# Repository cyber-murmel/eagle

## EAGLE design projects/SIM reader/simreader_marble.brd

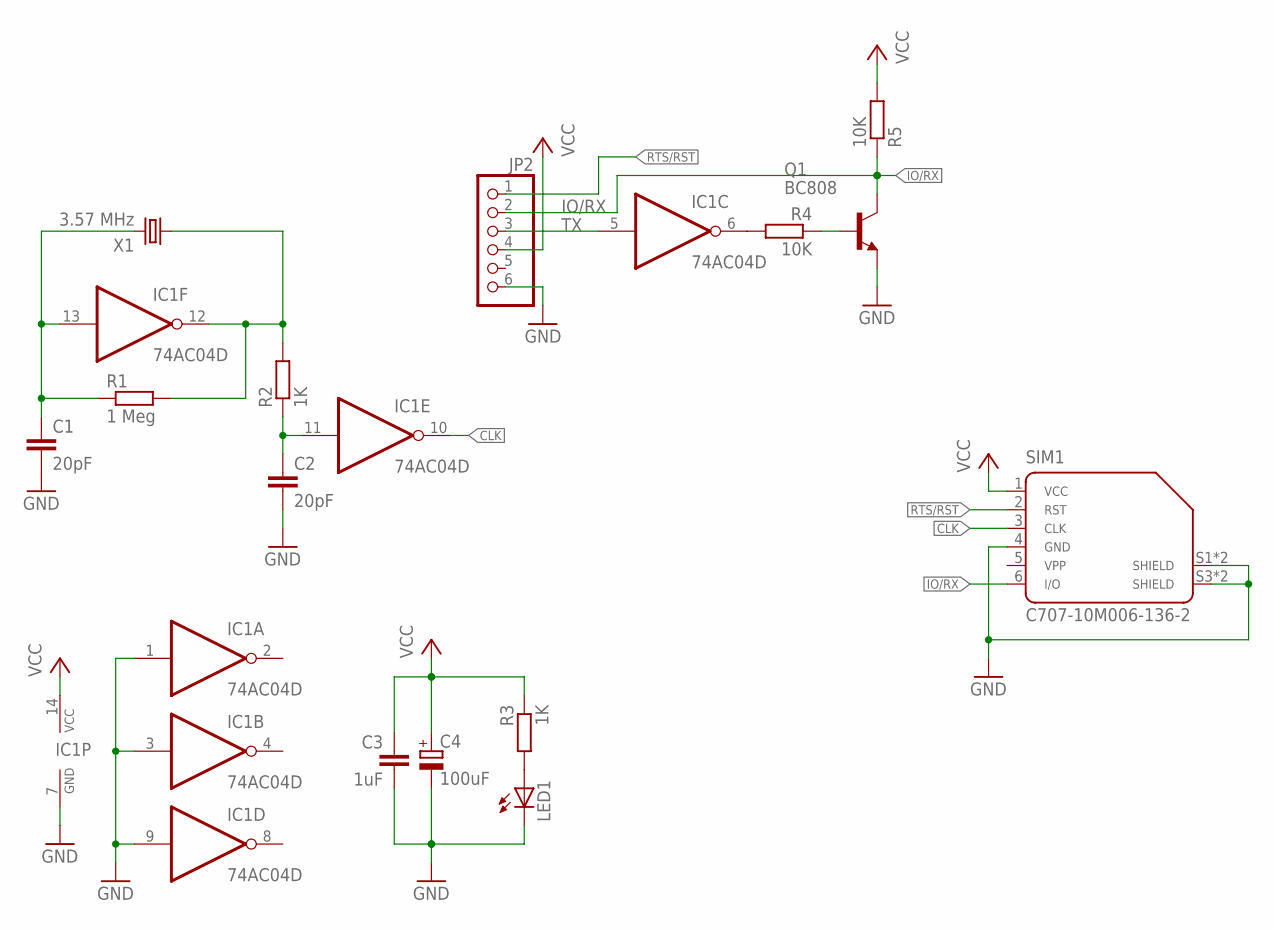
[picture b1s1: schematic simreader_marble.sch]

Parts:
C1, C2: 20pF; C0603
C3: 1uF; C0603
C4: 100uF; 140CLH-0810
IC1: 74AC04D; SO14
JP2: PINHD-1X6; 1X06
LED1: LEDCHIPLED_0603; CHIPLED_0603
Q1: BC808; SOT23-BEC
R1: 1 Meg; R0603
R2, R3: 1K; R0603
R4, R5: 10K; R0603
SIM1: C707-10M006-136-2; C707_10M006_136_2
X1: 3.57 MHz; HC49UP

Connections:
CLK: IC1.10 (O), SIM1.3
GND: C1.2, C2.2, C3.2, C4.-, IC1.1 (I), IC1.3 (I), IC1.7 (GND), IC1.9 (I), JP2.6, LED1.C, Q1.E, SIM1.4, SIM1.S1, SIM1.S2 (S1), SIM1.S3 (S2), SIM1.S4 (S2)
IO/RX: JP2.2, Q1.C, R5.1, SIM1.6
unnamed: C1.1, IC1.13 (I), R1.1, X1.2
unnamed: IC1.12 (O), R1.2, R2.2, X1.1
unnamed: C2.1, IC1.11 (I), R2.1
unnamed: IC1.6 (O), R4.2
unnamed: Q1.B, R4.1
unnamed: LED1.A, R3.2
RTS/RST: JP2.1, SIM1.2
TX: IC1.5 (I), JP2.3
VCC: C3.1, C4.+, IC1.14 (VCC), JP2.4, R3.1, R5.2, SIM1.1

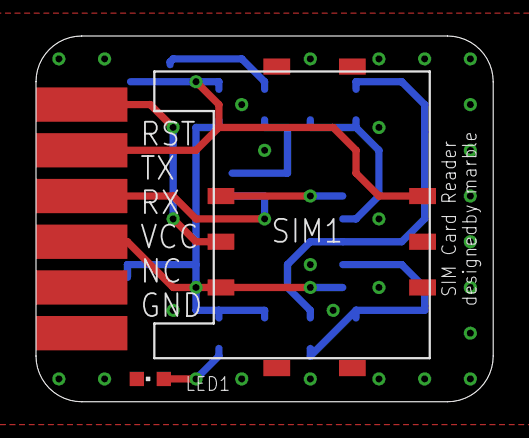
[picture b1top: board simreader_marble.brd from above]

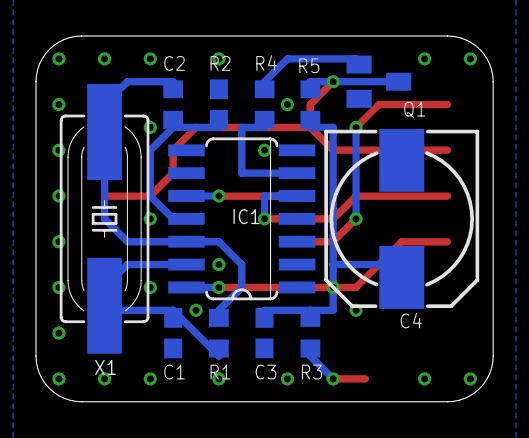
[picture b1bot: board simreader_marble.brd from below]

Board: 2 copper layers, 25.4 x 20.3 mm, 15 parts (12 on the bottom side), 12 nets.

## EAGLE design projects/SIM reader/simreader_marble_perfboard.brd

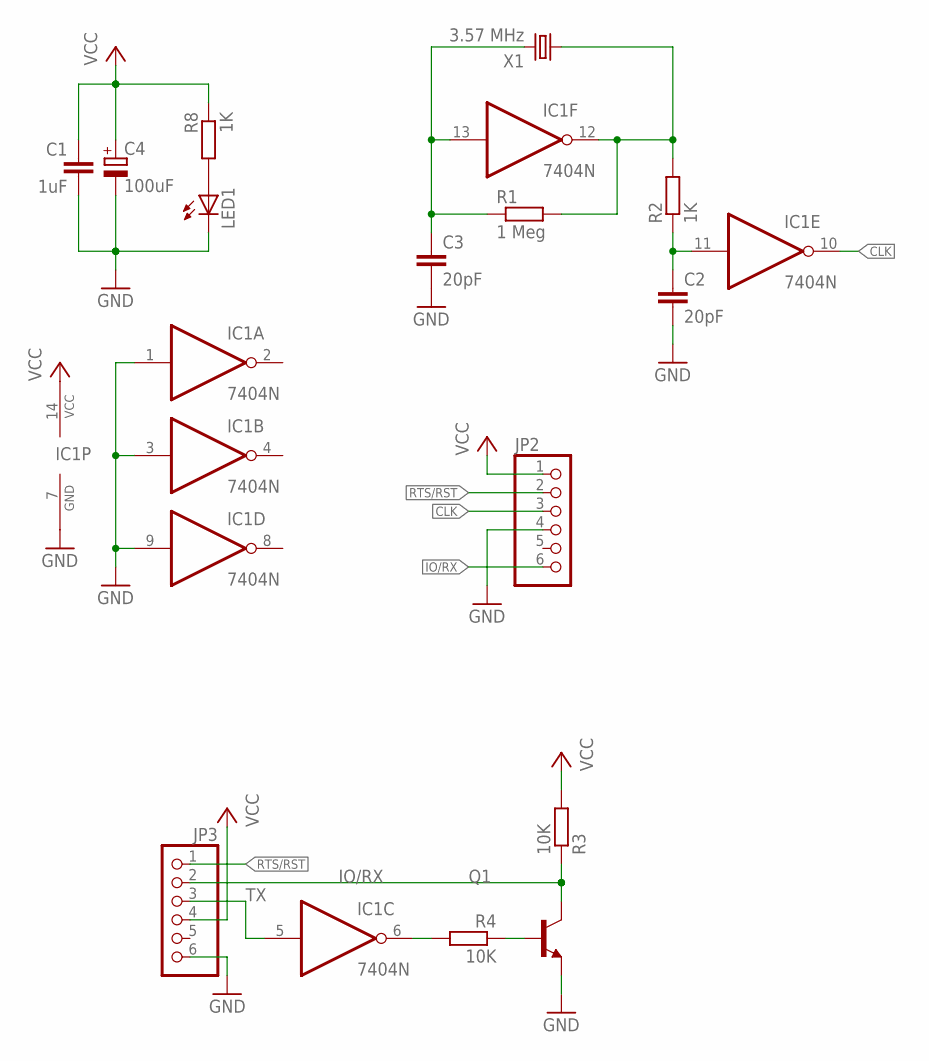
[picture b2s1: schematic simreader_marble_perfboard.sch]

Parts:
C1: 1uF; C050-024X044
C2, C3: 20pF; C050-024X044
C4: 100uF; B45181A
IC1: 7404N; DIL14
JP2, JP3: PINHD-1X6; 1X06
LED1: LED5MM
Q1: BC547-NPN-TO92-CBE; TO92-CBE
R1: 1 Meg; 0204/7
R2, R8: 1K; 0204/7
R3, R4: 10K; 0204/7
X1: 3.57 MHz; HC18U-V

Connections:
CLK: IC1.10 (O), JP2.3
GND: C1.2, C2.2, C3.2, C4.-, IC1.1 (I), IC1.3 (I), IC1.7 (GND), IC1.9 (I), JP2.4, JP3.6, LED1.K (C), Q1.E
IO/RX: JP2.6, JP3.2, Q1.C, R3.1
unnamed: C3.1, IC1.13 (I), R1.1, X1.2
unnamed: IC1.12 (O), R1.2, R2.2, X1.1
unnamed: C2.1, IC1.11 (I), R2.1
unnamed: IC1.6 (O), R4.2
unnamed: Q1.B, R4.1
unnamed: LED1.A, R8.2
RTS/RST: JP2.2, JP3.1
TX: IC1.5 (I), JP3.3
VCC: C1.1, C4.+, IC1.14 (VCC), JP2.1, JP3.4, R3.2, R8.1

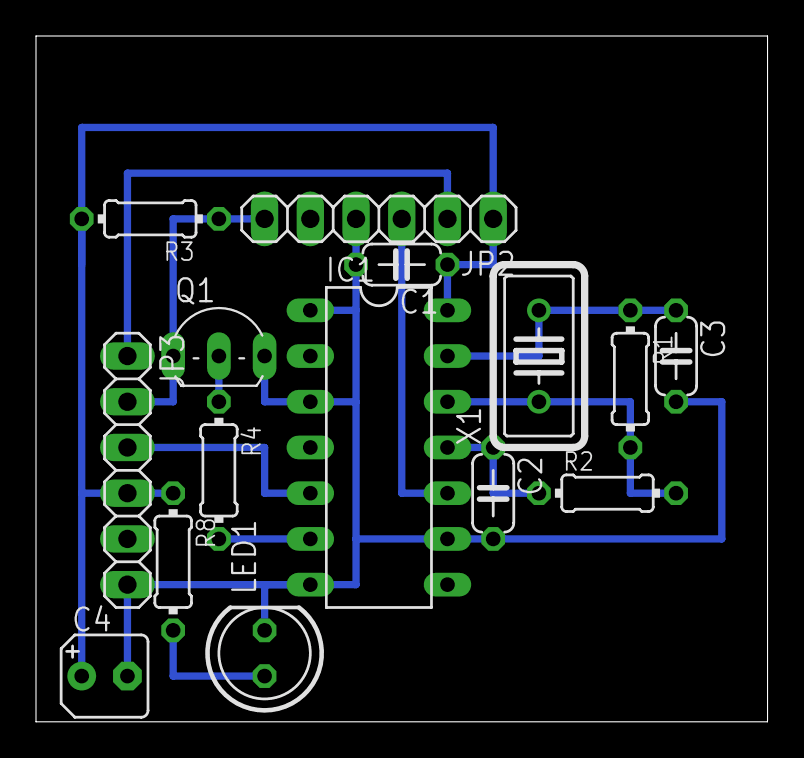
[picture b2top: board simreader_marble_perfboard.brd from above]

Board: 2 copper layers, 40.6 x 38.1 mm, 15 parts (0 on the bottom side), 12 nets.

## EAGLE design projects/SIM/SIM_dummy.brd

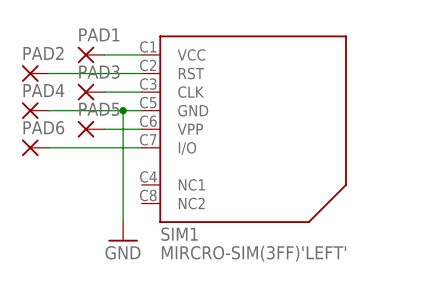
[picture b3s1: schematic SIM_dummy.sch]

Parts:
PAD1, PAD2, PAD3, PAD4, PAD5, PAD6: SMD2; SMD1,27-2,54
SIM1: MIRCRO-SIM(3FF)'LEFT'; MICRO-SIM_LEFT

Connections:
GND: PAD4.1, SIM1.C5 (GND)
unnamed: PAD6.1, SIM1.C7 (I/O)
unnamed: PAD2.1, SIM1.C2 (RST)
unnamed: PAD3.1, SIM1.C3 (CLK)
unnamed: PAD1.1, SIM1.C1 (VCC)
unnamed: PAD5.1, SIM1.C6 (VPP)

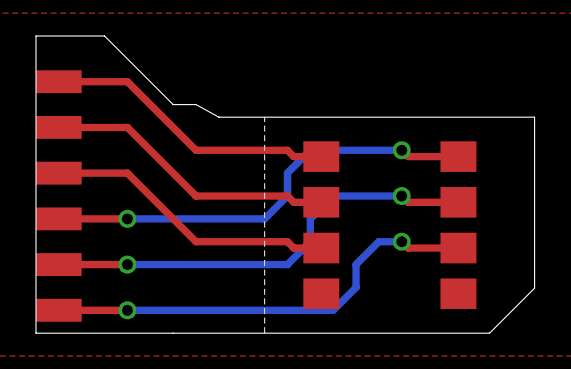
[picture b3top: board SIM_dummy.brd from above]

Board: 2 copper layers, 27.7 x 16.5 mm, 7 parts (0 on the bottom side), 6 nets.

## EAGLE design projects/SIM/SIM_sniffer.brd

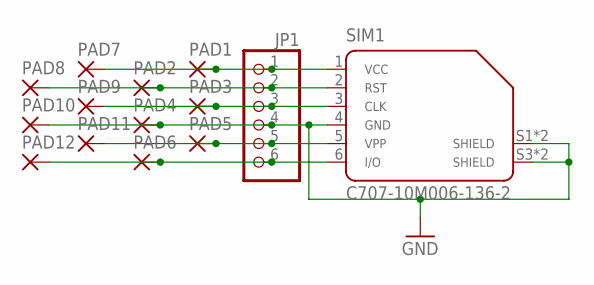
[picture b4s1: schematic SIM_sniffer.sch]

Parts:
JP1: PINHD-1X6; 1X06
PAD1, PAD2, PAD3, PAD4, PAD5, PAD6, PAD7, PAD8, PAD9, PAD10, PAD11, PAD12: SMD2; SMD1,27-2,54
SIM1: C707-10M006-136-2; C707_10M006_136_2

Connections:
GND: JP1.4, PAD4.1, PAD10.1, SIM1.4, SIM1.S1, SIM1.S2 (S1), SIM1.S3 (S2), SIM1.S4 (S2)
unnamed: JP1.6, PAD6.1, PAD12.1, SIM1.6
unnamed: JP1.2, PAD2.1, PAD8.1, SIM1.2
unnamed: JP1.3, PAD3.1, PAD9.1, SIM1.3
unnamed: JP1.1, PAD1.1, PAD7.1, SIM1.1
unnamed: JP1.5, PAD5.1, PAD11.1, SIM1.5

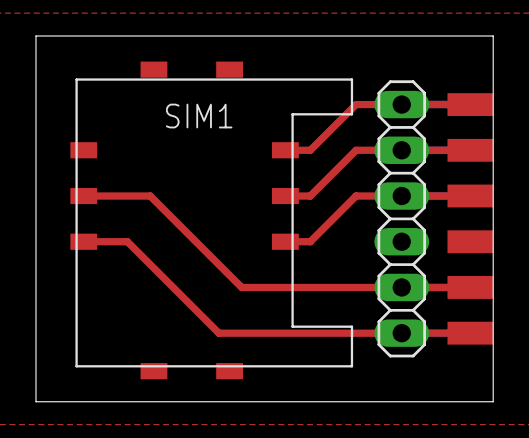
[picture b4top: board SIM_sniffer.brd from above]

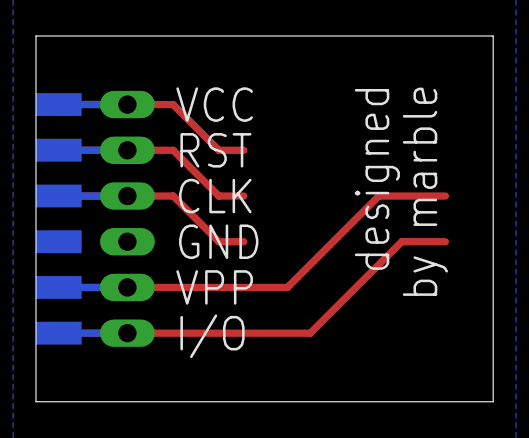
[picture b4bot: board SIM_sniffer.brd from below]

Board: 2 copper layers, 25.4 x 20.3 mm, 14 parts (6 on the bottom side), 6 nets.
